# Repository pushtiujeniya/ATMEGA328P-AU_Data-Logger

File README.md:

# MCU Data Logger — ATmega328P + RTC + External dual EEPROM

# Features

- ATmega328P-AU AVR Microcontroller
- Dual 24LC1025 External EEPROMs
- DS1337S RTC (Real Time Clock)
- I2C Communication Bus
- UART Header
- SPI Programming Header
- External Crystal Oscillator
- Battery Powered Design
- Compact 2-Layer PCB
- GPIO Breakout Header
- RTC Backup Support

# Hardware Overview

## 1. Microcontroller

### ATmega328P-AU
Main controller used for:
- Data processing
- lower power consumption
- EEPROM communication
- RTC communication
- GPIO handling
- UART communication

### MCU Clock
- 16 MHz Crystal Oscillator
- Two 22 pF load capacitors

### Reset Circuit
- 10k pull-up resistor on RESET pin to keep the reset pin high in normal mode

### Power Decoupling
- 0.1uF decoupling capacitor near VCC  for power stabliity 

# Memory Storage

## External EEPROM

Two external EEPROM ICs are used:

- 24LC1025
- 24LC1025

### Communication
- I2C Protocol

### EEPROM Features
- Non-volatile memory
- Long-term data retention
- Byte and page write support

### Address Configuration

#### EEPROM U2
- A0 = VCC
- A1 = VCC
- A2 = VCC

#### EEPROM U3
- A0 = GND
- A1 = VCC
- A2 = VCC

This allows both EEPROMs to operate on the same I2C bus with different addresses.

### I2C Pull-up Resistors
- SDA → 4.7kΩ pull-up
- SCL → 4.7kΩ pull-up

# RTC Section
## DS1337S Real-Time Clock

Used for:
- Timekeeping
- Timestamp generation
- Scheduled logging
- supports battery backup oscillator

### RTC Crystal
- 32.768 kHz crystal oscillator

### RTC Interrupt
INT/SQW output available for:
- Alarm interrupt
- Periodic wakeup
---
# Communication Interfaces

## I2C Header
Exposed pins:
- SDA
- SCL
- VCC
- GND
  
Used for:
- External sensor connection
- Additional peripherals
  
## UART Header
Exposed pins:
- RX
- TX
- VCC
- GND
Used for:
- Serial debugging
- PC communication
- Data extraction
  
## SPI Header
6-pin SPI programming interface:
- MOSI
- MISO
- SCK
- RESET
- VCC
- GND

Used for:
- Bootloader flashing
- Firmware upload
  
# GPIO Header

Digital GPIO breakout:
- D2
- D3
- D4
- D5
- D6
- D7
- D8
- VCC
- GND

Used for:
- Sensor interfacing
- Digital peripherals
- Expansion

# Power System

## Input Power
Battery-powered design.

### Power Indicator
LED with 330Ω current-limiting resistor.

### Decoupling Capacitors
Used near IC power pins for:
- Noise reduction
- Stable operation

---

# PCB Design

## PCB Specifications

- 2-Layer PCB
- Through-hole + SMD mixed design
- Compact embedded layout
- NPTH Mounting holes provided for pcb support
  
### Design Considerations

- Separate signal routing
- Short I2C traces
- Pull-up resistors near bus
- Ground return optimization
- Crystal traces kept short

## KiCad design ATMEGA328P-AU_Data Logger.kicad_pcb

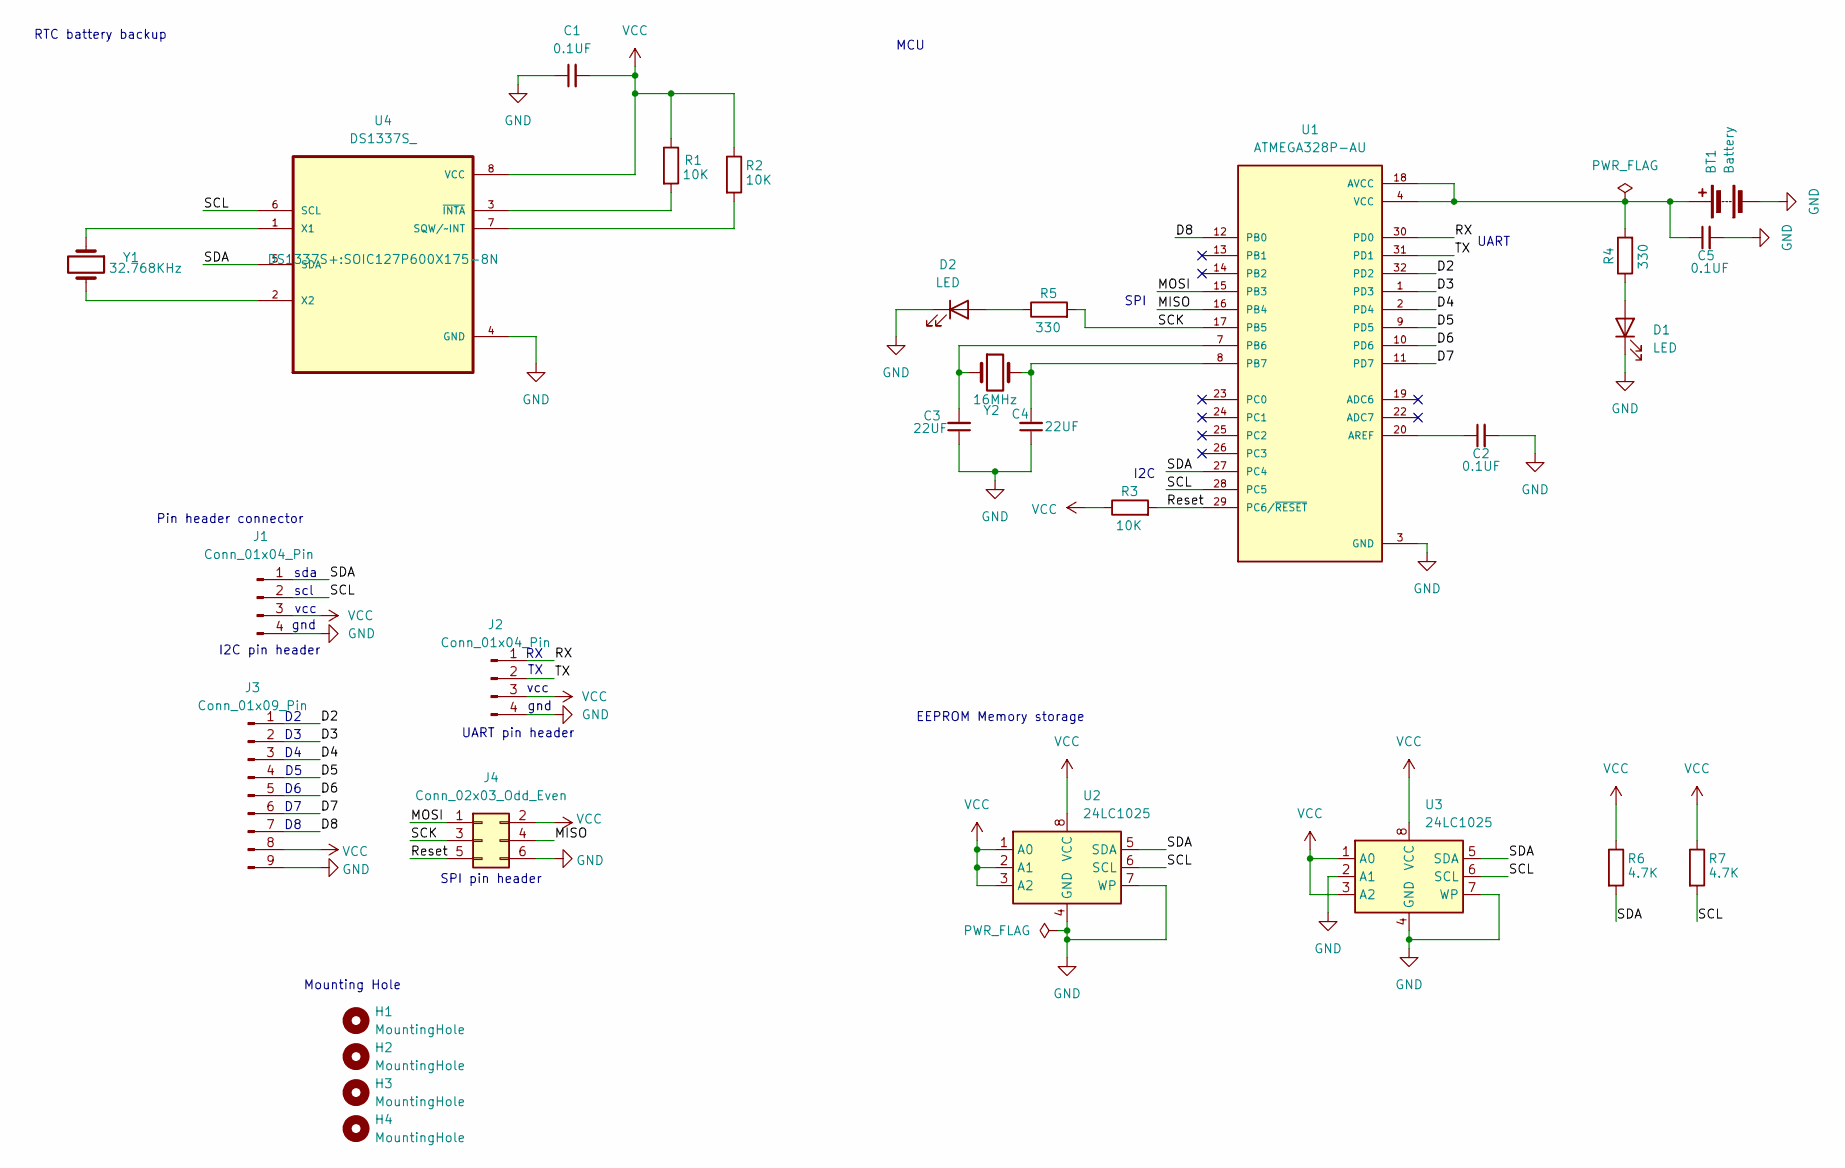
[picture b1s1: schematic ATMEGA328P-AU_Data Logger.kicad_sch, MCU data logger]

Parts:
BT1: Battery; PinHeader_1x02_P2.54mm_Vertical
C1, C2, C5: 0.1UF; C_0805_2012Metric
C3, C4: 22UF; C_0805_2012Metric
D1, D2: LED; LED_0603_1608Metric
H1, H2, H3, H4: MountingHole; MountingHole_3.2mm_M3
J1, J2: Conn_01x04_Pin; PinHeader_1x04_P2.54mm_Vertical
J3: Conn_01x09_Pin; PinHeader_1x09_P2.54mm_Vertical
J4: Conn_02x03_Odd_Even; PinHeader_2x03_P2.54mm_Vertical
R1, R2, R3: 10K; R_0805_2012Metric
R4, R5: 330; R_0805_2012Metric
R6, R7: 4.7K; R_0805_2012Metric
U1: ATMEGA328P-AU; QFP80P900X900X120-32N; PARTREV 8271A
U2, U3: 24LC1025; SOIC-8_5.3x5.3mm_P1.27mm
U4: DS1337S_; SOIC127P600X175-8N
Y1: 32.768KHz; Crystal_SMD_5032-2Pin_5.0x3.2mm_HandSoldering
Y2: 16MHz; Crystal_SMD_5032-2Pin_5.0x3.2mm_HandSoldering

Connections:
/D2: J3.1, U1.32 (PD2)
/D3: J3.2, U1.1 (PD3)
/D4: J3.3, U1.2 (PD4)
/D5: J3.4, U1.9 (PD5)
/D6: J3.5, U1.10 (PD6)
/D7: J3.6, U1.11 (PD7)
/D8: J3.7, U1.12 (PB0)
/MISO: J4.4, U1.16 (PB4)
/MOSI: J4.1, U1.15 (PB3)
/RX: J2.1, U1.30 (PD0)
/Reset: J4.5, R3.2, U1.29 (PC6/~RESET)
/SCK: J4.3, R5.2, U1.17 (PB5)
/SCL: J1.2, R7.2, U1.28 (PC5), U2.6 (SCL), U3.6 (SCL), U4.6 (SCL)
/SDA: J1.1, R6.2, U1.27 (PC4), U2.5 (SDA), U3.5 (SDA), U4.5 (SDA)
/TX: J2.2, U1.31 (PD1)
GND: BT1.2 (-), C1.1, C2.2, C3.1, C4.1, C5.2, D1.1 (K), D2.1 (K), J1.4, J2.4, J3.9, J4.6, U1.3 (GND), U1.5 (GND), U1.21 (GND), U2.4 (GND), U2.7 (WP), U3.2 (A1), U3.4 (GND), U3.7 (WP), U4.4 (GND)
unnamed: D1.2 (A), R4.1
unnamed: D2.2 (A), R5.1
unnamed: C2.1, U1.20 (AREF)
unnamed: C3.2, U1.7 (PB6), Y2.1
unnamed: C4.2, U1.8 (PB7), Y2.2
unnamed: R2.2, U4.7 (SQW/~INT)
unnamed: U4.1 (X1), Y1.1
unnamed: U4.2 (X2), Y1.2
unnamed: R1.2, U4.3 (~INTA)

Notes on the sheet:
UART
Pin header connector
I2C pin header
vcc
RTC battery backup
gnd
SPI
sda
Mounting Hole
MCU
I2C
UART pin header
SPI pin header
scl
EEPROM Memory storage

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
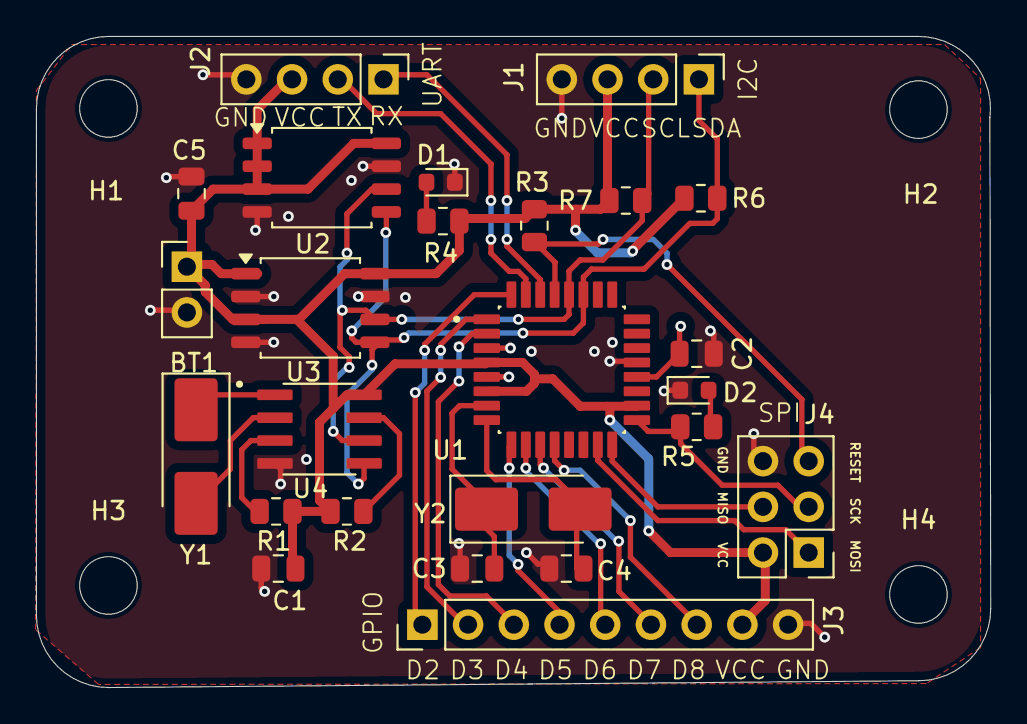
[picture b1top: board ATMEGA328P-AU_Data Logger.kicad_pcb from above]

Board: 2 copper layers, 53.0 x 36.2 mm, 29 parts (0 on the bottom side), 26 nets.

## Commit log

2026-05-10 Add temp file to External Library
2026-05-10 Add temp file in ATMEGA328P-AU directory
2026-05-10 atmega328p-au symbol and step file added
2026-05-10 atmega328p-au footprint file added
2026-05-10 Add temp file to DS1337S directory
2026-05-10 symbol and step file added
2026-05-10 footprint file added
2026-05-10 Add temp file in 3D view directory
2026-05-10 3D view images added
2026-05-10 schematic and layout file added
2026-05-10 schematic file added
2026-05-10 layout file added
2026-05-10 project file added
2026-05-10 Create temp
2026-05-10 back up files added
2026-05-11 Revise README with comprehensive project details
    Updated README to provide detailed project features, hardware overview, memory storage, communication interfaces, GPIO header, power system, and PCB design specifications.
2026-05-11 Technical document pdf file added
